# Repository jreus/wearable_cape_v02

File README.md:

# wearable_cape_v02

Second version of a wearable sensing/actuating cape for the Augmented Attention Lab (June 2019)

## Changes from v01
- fixed wiring errors from filter circuits to minijack outputs
- removed unused resistors from filter design (two in final stage, one in input stage)
- swapped out resistor-based voltage divider for a dedicated 1.8V reference (MAX6100)
- breakout header for analog inputs
- widen power rail traces from battery to 11.1V source to amplifiers

# 23 MAY 2019 ~ WARNING! First Boards Ordered from Eurocircuits have wiring mistakes!
There was a serious wiring error in these boards, where the 10-pin row of headers that
connect downward into the Bela's analog inputs row and analog outputs row are reversed!
These headers do not correctly match up to the pins on the Bela and thus need to be
sliced and re-routed on the capelet board.

The pin ordering is flipped. So for example, on the Bela, the ground header for analog inputs is
on the bottom. But on the capelet it's at the top.

Likewise, on the Bela the analog outputs ground is on the right, on the capelet it's on the
left.

Possible Solutions (other than making new boards!):

1. Make a pin header/wire adapter that reverses the connections
2. Cut n rewire the capelet

See images/REV2.1_wiring_mistake for more info on the wiring issue...

## More errors
The mode select and halt switches are misnamed on the board, and potentially miswired to the breakout board header.

The actual wiring of the status header on the v2 board is...

1 ~ GND
2 ~ STATUS_LED
3 ~ D11
4 ~ SW_HALT
5 ~ D8
6 ~ MODE_SEL1 / 3v3
7 ~ D9
8 ~ MODE_SEL2

## ToDos (future work)
- Add bypass capacitors to the active filters
- silkscreen labels for switch functionality and outputs
- breakout capability of mode switch, reset switch, & status LEDs
  - user leds, see: http://beaglebone.cameon.net/home/using-the-user-leds
- add additional 2-channel output for full access to all output channels

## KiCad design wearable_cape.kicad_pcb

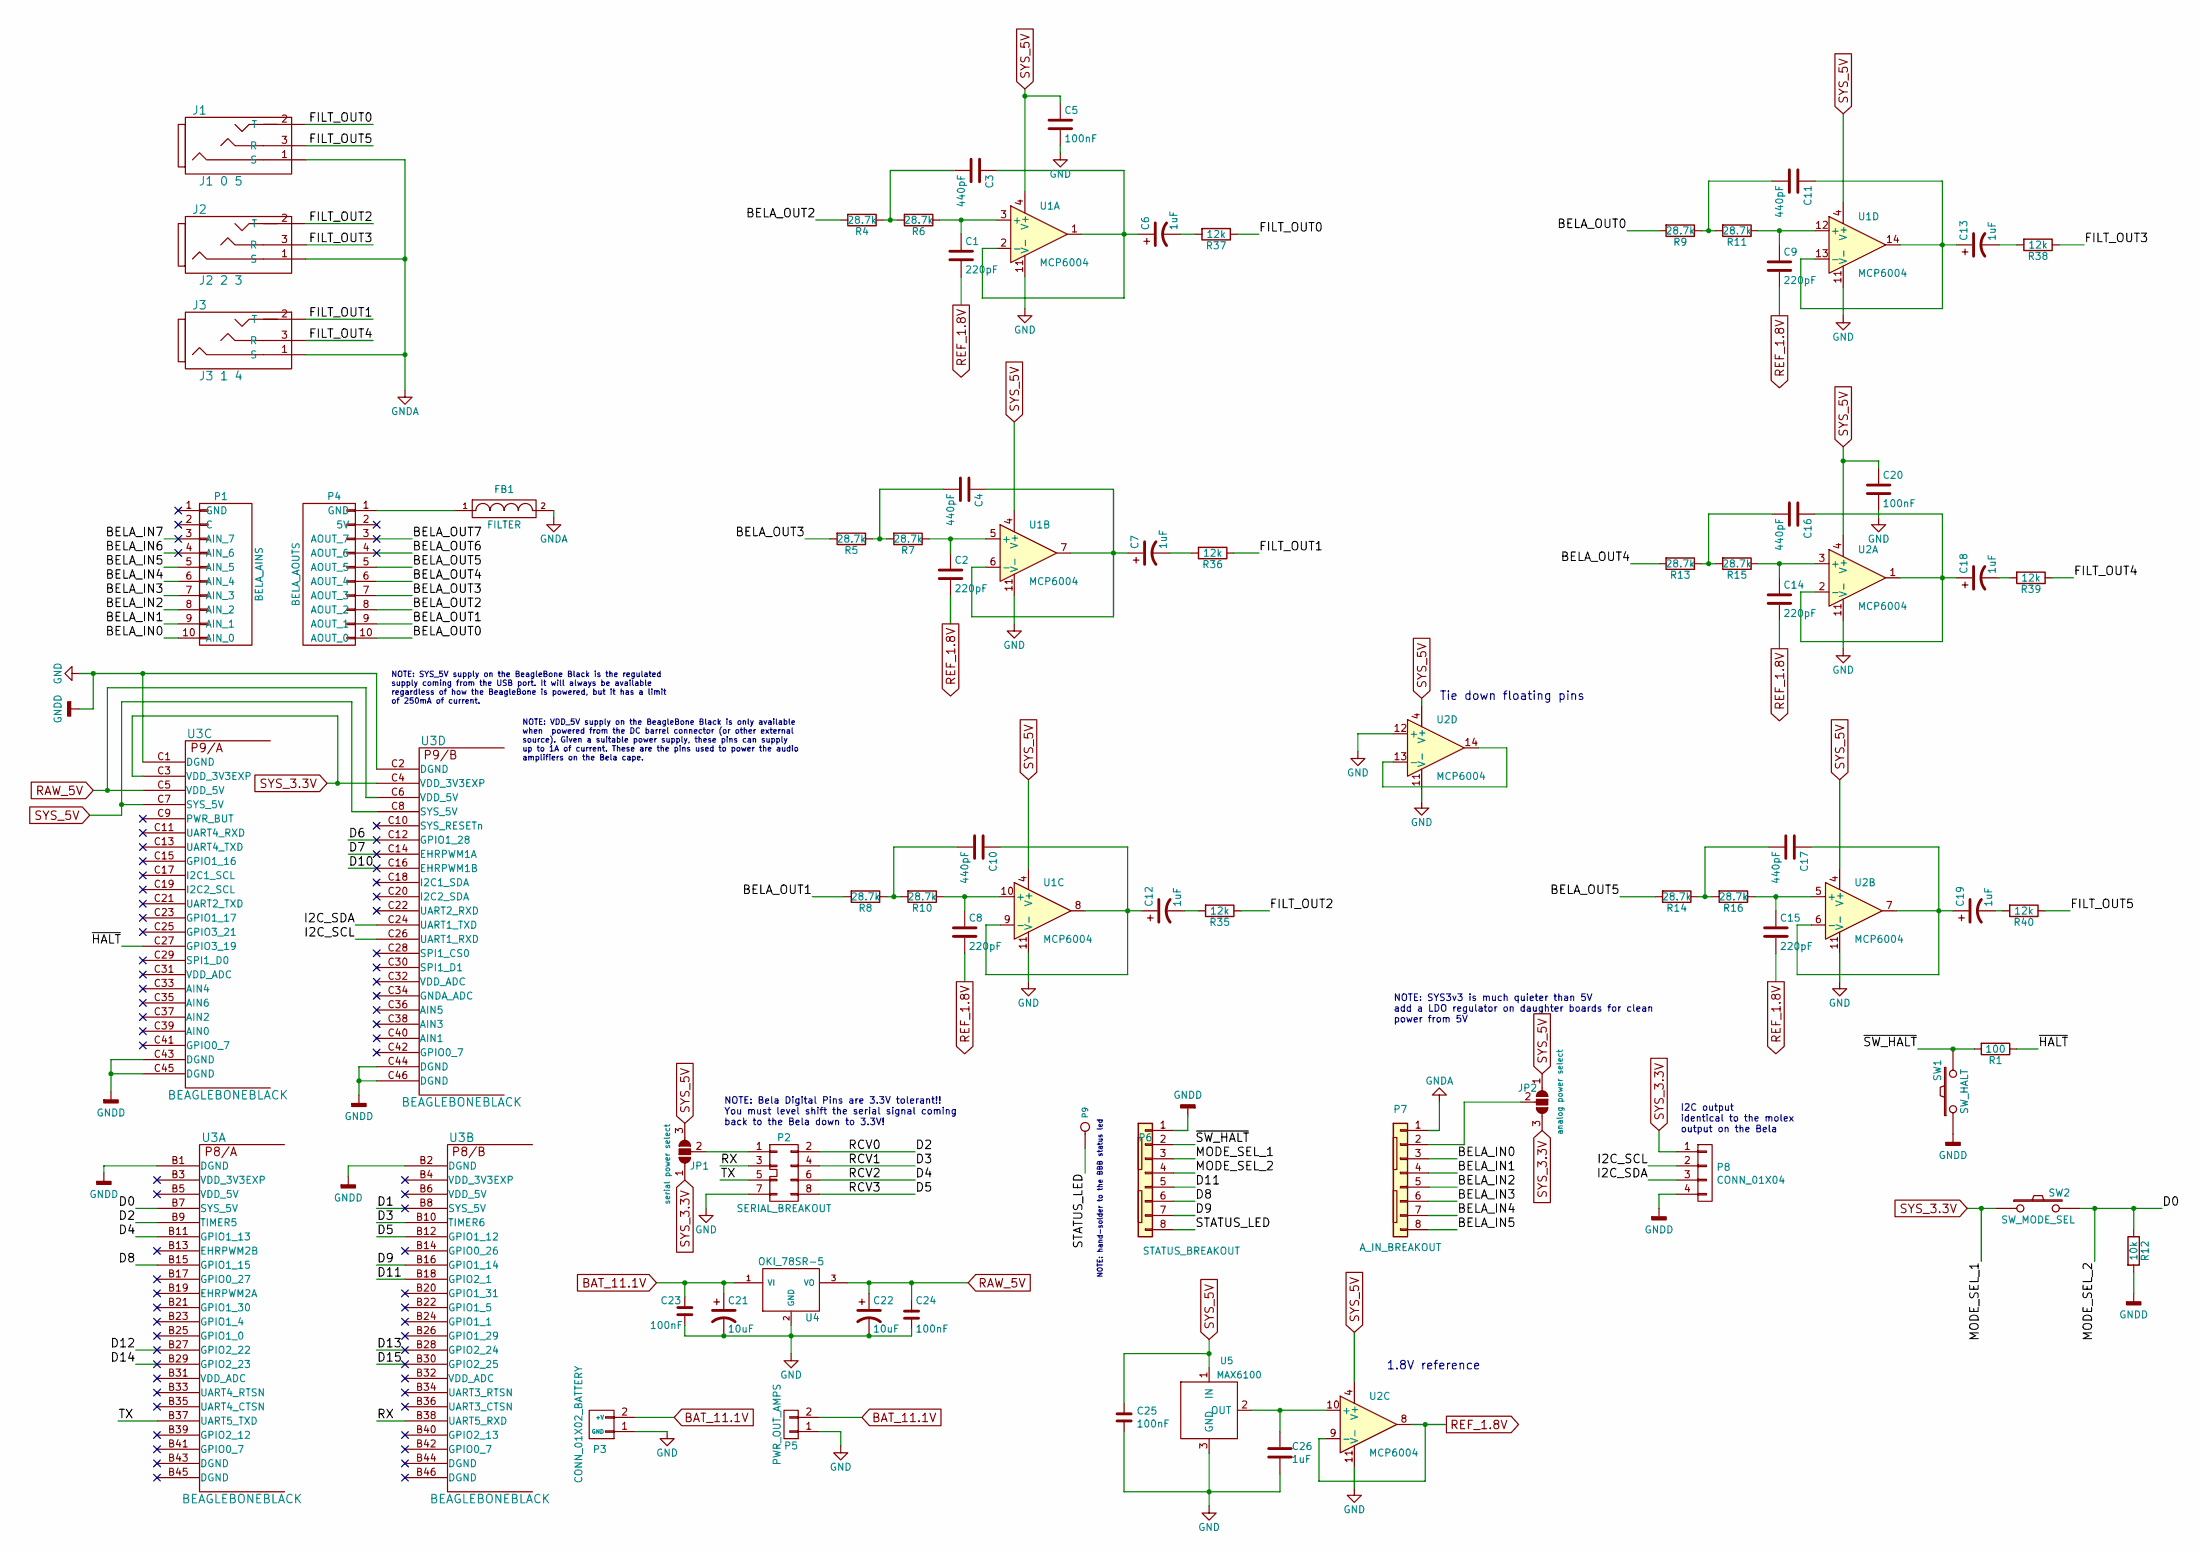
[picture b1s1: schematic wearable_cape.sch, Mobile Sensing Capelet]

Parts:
C1, C2, C8, C9, C14, C15: 220pF; C_0603_SMD_HandSolder
C3, C4, C10, C11, C16, C17: 440pF; C_0603_SMD_HandSolder
C5, C20, C23, C24, C25: 100nF; C_0603_SMD_HandSolder
C6, C7, C12, C13, C18, C19, C26: 1uF; C_1206
C21, C22: 10uF; C_1210
FB1: FILTER; L_0603_SMD_Handsolder
J1: J1 0 5; Lumberg_1503_03
J2: J2 2 3; Lumberg_1503_03
J3: J3 1 4; Lumberg_1503_03
JP1: serial power select; SolderJumper-3_P1.3mm_Open_Pad1.0x1.5mm
JP2: analog power select; SolderJumper-3_P1.3mm_Open_Pad1.0x1.5mm
P1: BELA_AINS; PinHeader_1x10_P2.54mm_Vertical
P2: SERIAL_BREAKOUT; IDC-Header_2x04_P2.54mm_Vertical
P3: CONN_01X02_BATTERY; TerminalBlock_Phoenix_PT_H_1x02_P3.50mm
P4: BELA_AOUTS; PinHeader_1x10_P2.54mm_Vertical
P5: PWR_OUT_AMPS; TerminalBlock_Phoenix_MPT_1x02_P2.54mm
P6: STATUS_BREAKOUT; Molex_KK-254_1x08_P2.54mm_Vertical
P7: A_IN_BREAKOUT; Molex_KK-254_1x08_P2.54mm_Vertical
P8: CONN_01X04; Molex_KK-254_1x04_P2.54mm_Vertical
P9: CONN_1; PinHeader_1x01_P2.54mm_Vertical
R1: 100; R_0603_SMD_Handsolder
R4, R5, R6, R7, R8, R9, R10, R11, R13, R14, R15, R16: 28.7k; R_0603_SMD_Handsolder
R12: 10k; R_0603_SMD_Handsolder
R35, R36, R37, R38, R39, R40: 12k; R_0603_SMD_Handsolder
SW1: SW_HALT; SW_SPST_EVQPE1
SW2: SW_MODE_SEL; SW_SPST_EVQPE1
U1, U2: MCP6004; SOIC-14_3.9x8.7mm_P1.27mm
U3: BEAGLEBONEBLACK; beagleboneblack_nomount
U4: OKI_78SR-5; Converter_DCDC_muRata_OKI-78SR_Horizontal
U5: MAX6100; SOT-23

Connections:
/BELA_IN0: P1.10 (AIN_0), P7.3
/BELA_IN1: P1.9 (AIN_1), P7.4
/BELA_IN2: P1.8 (AIN_2), P7.5
/BELA_IN3: P1.7 (AIN_3), P7.6
/BELA_IN4: P1.6 (AIN_4), P7.7
/BELA_IN5: P1.5 (AIN_5), P7.8
/BELA_IN6: P1.4 (AIN_6)
/BELA_IN7: P1.3 (AIN_7)
/BELA_OUT0: P4.10 (AOUT_0), R9.2
/BELA_OUT1: P4.9 (AOUT_1), R8.2
/BELA_OUT2: P4.8 (AOUT_2), R4.2
/BELA_OUT3: P4.7 (AOUT_3), R5.2
/BELA_OUT4: P4.6 (AOUT_4), R13.2
/BELA_OUT5: P4.5 (AOUT_5), R14.2
/BELA_OUT6: P4.4 (AOUT_6)
/BELA_OUT7: P4.3 (AOUT_7)
/D0: P6.4, R12.1, SW2.2, U3.B7 (SYS_5V)
/D1: U3.B8 (SYS_5V)
/D2: P2.2, U3.B9 (TIMER5)
/D3: P2.4, U3.B10 (TIMER6)
/D4: P2.6, U3.B11 (GPIO1_13)
/D5: P2.8, U3.B12 (GPIO1_12)
/D6: U3.C12 (GPIO1_28)
/D7: U3.C14 (EHRPWM1A)
/D8: P6.6, U3.B15 (GPIO1_15)
/D9: P6.7, U3.B16 (GPIO1_14)
/D10: U3.C16 (EHRPWM1B)
/D11: P6.5, U3.B18 (GPIO2_1)
/D12: U3.B27 (GPIO2_22)
/D13: U3.B28 (GPIO2_24)
/D14: U3.B29 (GPIO2_23)
/D15: U3.B30 (GPIO2_25)
/FILT_OUT0: J1.2 (T), R37.1
/FILT_OUT1: J3.2 (T), R36.1
/FILT_OUT2: J2.2 (T), R35.1
/FILT_OUT3: J2.3 (R), R38.1
/FILT_OUT4: J3.3 (R), R39.1
/FILT_OUT5: J1.3 (R), R40.1
/I2C_SCL: P8.2, U3.C26 (UART1_RXD)
/I2C_SDA: P8.3, U3.C24 (UART1_TXD)
/RX: P2.3, U3.B38 (UART5_RXD)
/STATUS_LED: P6.8, P9.1
/TX: P2.5, U3.B37 (UART5_TXD)
/~HALT: R1.1, U3.C27 (GPIO3_19)
/~SW_HALT: P6.2, R1.2, SW1.2
BAT_11.1V: C21.1, C23.1, P3.2 (+V), P5.2, U4.1 (VI)
GND: C5.2, C20.2, C21.2, C22.2, C23.2, C24.2, C25.2, C26.2, P2.7, P3.1 (GND), P5.1, P6.1, P8.4, R12.2, SW1.1, U1.11 (V-), U2.11 (V-), U2.12 (+), U3.B1 (DGND), U3.B2 (DGND), U3.C1 (DGND), U3.C2 (DGND), U3.C43 (DGND), U3.C44 (DGND), U3.C45 (DGND), U3.C46 (DGND), U4.2 (GND), U5.3 (GND)
GNDA: FB1.2, J1.1 (S), J2.1 (S), J3.1 (S), P7.1
unnamed: C1.1, R6.1, U1.3 (+)
unnamed: C2.1, R7.1, U1.5 (+)
unnamed: C3.1, C6.1, U1.1, U1.2 (-)
unnamed: C3.2, R4.1, R6.2
unnamed: C4.1, C7.1, U1.6 (-), U1.7
unnamed: C4.2, R5.1, R7.2
unnamed: C6.2, R37.2
unnamed: C7.2, R36.2
unnamed: C8.1, R10.1, U1.10 (+)
unnamed: C9.1, R11.1, U1.12 (+)
unnamed: C10.1, C12.1, U1.8, U1.9 (-)
unnamed: C10.2, R8.1, R10.2
unnamed: C11.1, C13.1, U1.13 (-), U1.14
unnamed: C11.2, R9.1, R11.2
unnamed: C12.2, R35.2
unnamed: C13.2, R38.2
unnamed: C14.1, R15.1, U2.3 (+)
unnamed: C15.1, R16.1, U2.5 (+)
unnamed: C16.1, C18.1, U2.1, U2.2 (-)
unnamed: C16.2, R13.1, R15.2
unnamed: C17.1, C19.1, U2.6 (-), U2.7
unnamed: C17.2, R14.1, R16.2
unnamed: C18.2, R39.2
unnamed: C19.2, R40.2
unnamed: C26.1, U2.10 (+), U5.2 (OUT)
unnamed: FB1.1, P4.1 (GND)
unnamed: JP1.2 (C), P2.1
unnamed: JP2.2 (C), P7.2
unnamed: U2.13 (-), U2.14
RAW_5V: C22.1, C24.1, U3.C5 (VDD_5V), U3.C6 (VDD_5V), U4.3 (VO)
REF_1.8V: C1.2, C2.2, C8.2, C9.2, C14.2, C15.2, U2.8, U2.9 (-)
SYS_3.3V: JP1.1 (A), JP2.3 (B), P6.3, P8.1, SW2.1, U3.C3 (VDD_3V3EXP), U3.C4 (VDD_3V3EXP)
SYS_5V: C5.1, C20.1, C25.1, JP1.3 (B), JP2.1 (A), U1.4 (V+), U2.4 (V+), U3.C7 (SYS_5V), U3.C8 (SYS_5V), U5.1 (IN)

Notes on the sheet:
1.8V reference
I2C output identical to the molex output on the Bela
NOTE: SYS3v3 is much quieter than 5V add a LDO regulator on daughter boards for clean power from 5V
NOTE: hand-solder to the BBB status led
Tie down floating pins
NOTE: Bela Digital Pins are 3.3V tolerant!! You must level shift the serial signal coming back to the Bela down to 3.3V!
NOTE: SYS_5V supply on the BeagleBone Black is the regulated supply coming from the USB port. It will always be available regardless of how the BeagleBone is powered, but it has a limit of 250mA of current.
NOTE: VDD_5V supply on the BeagleBone Black is only available when powered from the DC barrel connector (or other external source). Given a suitable power supply, these pins can supply up to 1A of current. These are the pins used to power the audio amplifiers on the Bela cape.

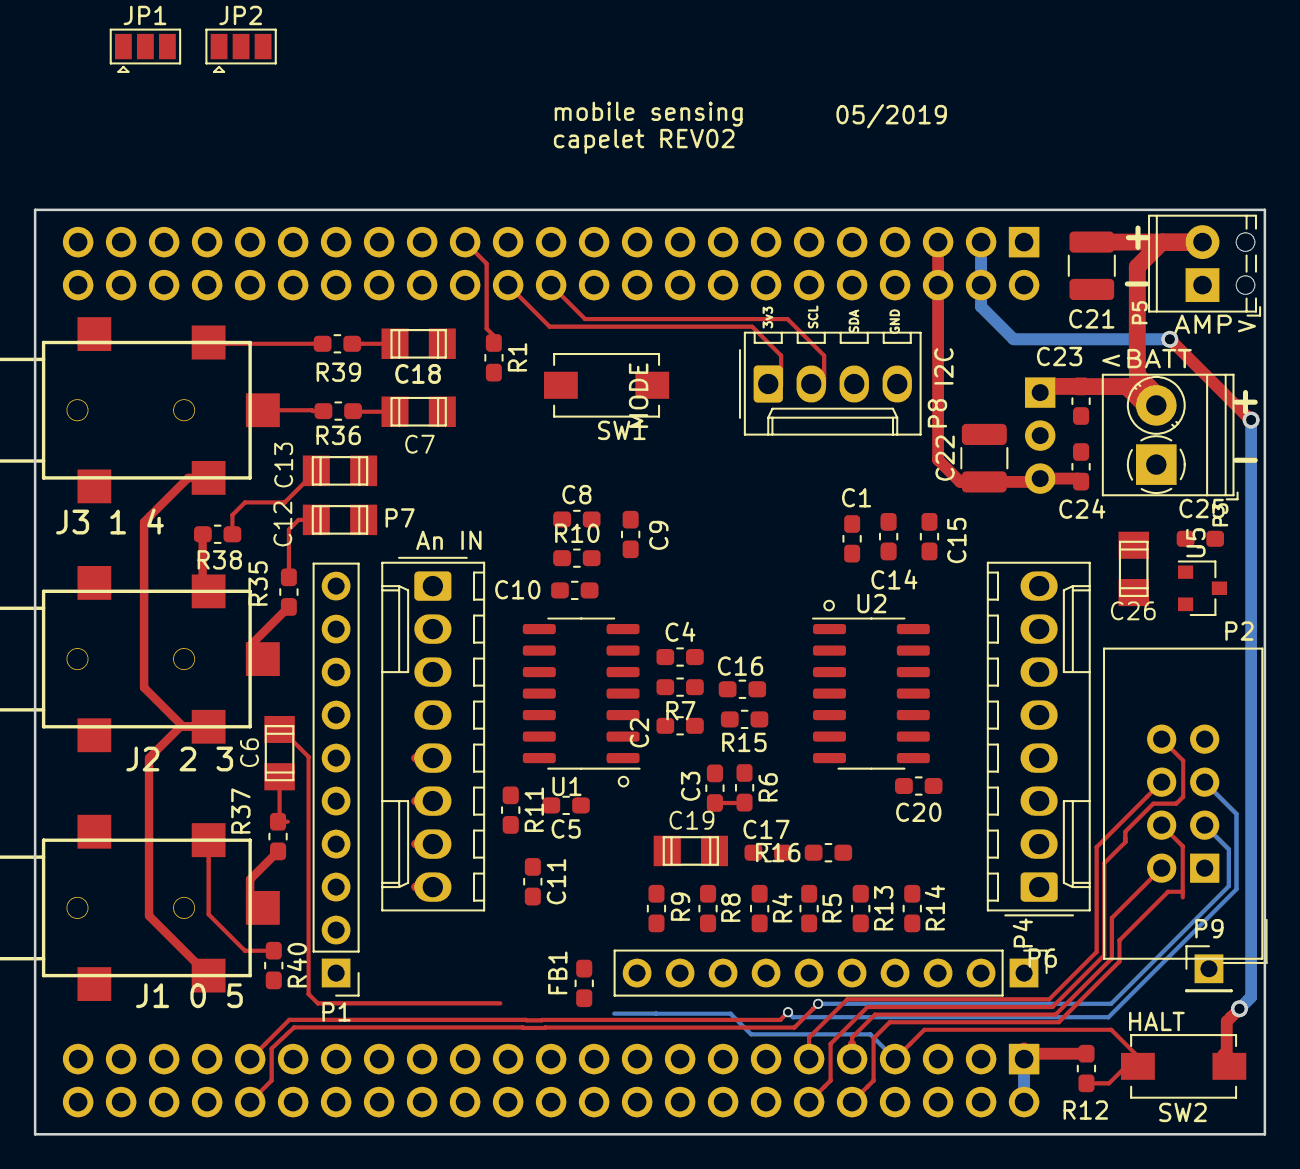
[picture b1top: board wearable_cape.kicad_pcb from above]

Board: 2 copper layers, 72.6 x 54.6 mm, 68 parts (1 on the bottom side), 69 nets.

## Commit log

2020-09-06 updates - wiring mistake!
2020-09-07 updates to v2 schematics with notations on wiring errors
